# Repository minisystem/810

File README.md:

SYSTEM80 810
======================================

VCO/VCF/VCA in Eurorack format. Currently under development.

Hardware design by Minisystem: info@system80.net

LICENSE
=======
cc by-nc-sa
https://creativecommons.org/licenses/by-nc-sa/4.0/

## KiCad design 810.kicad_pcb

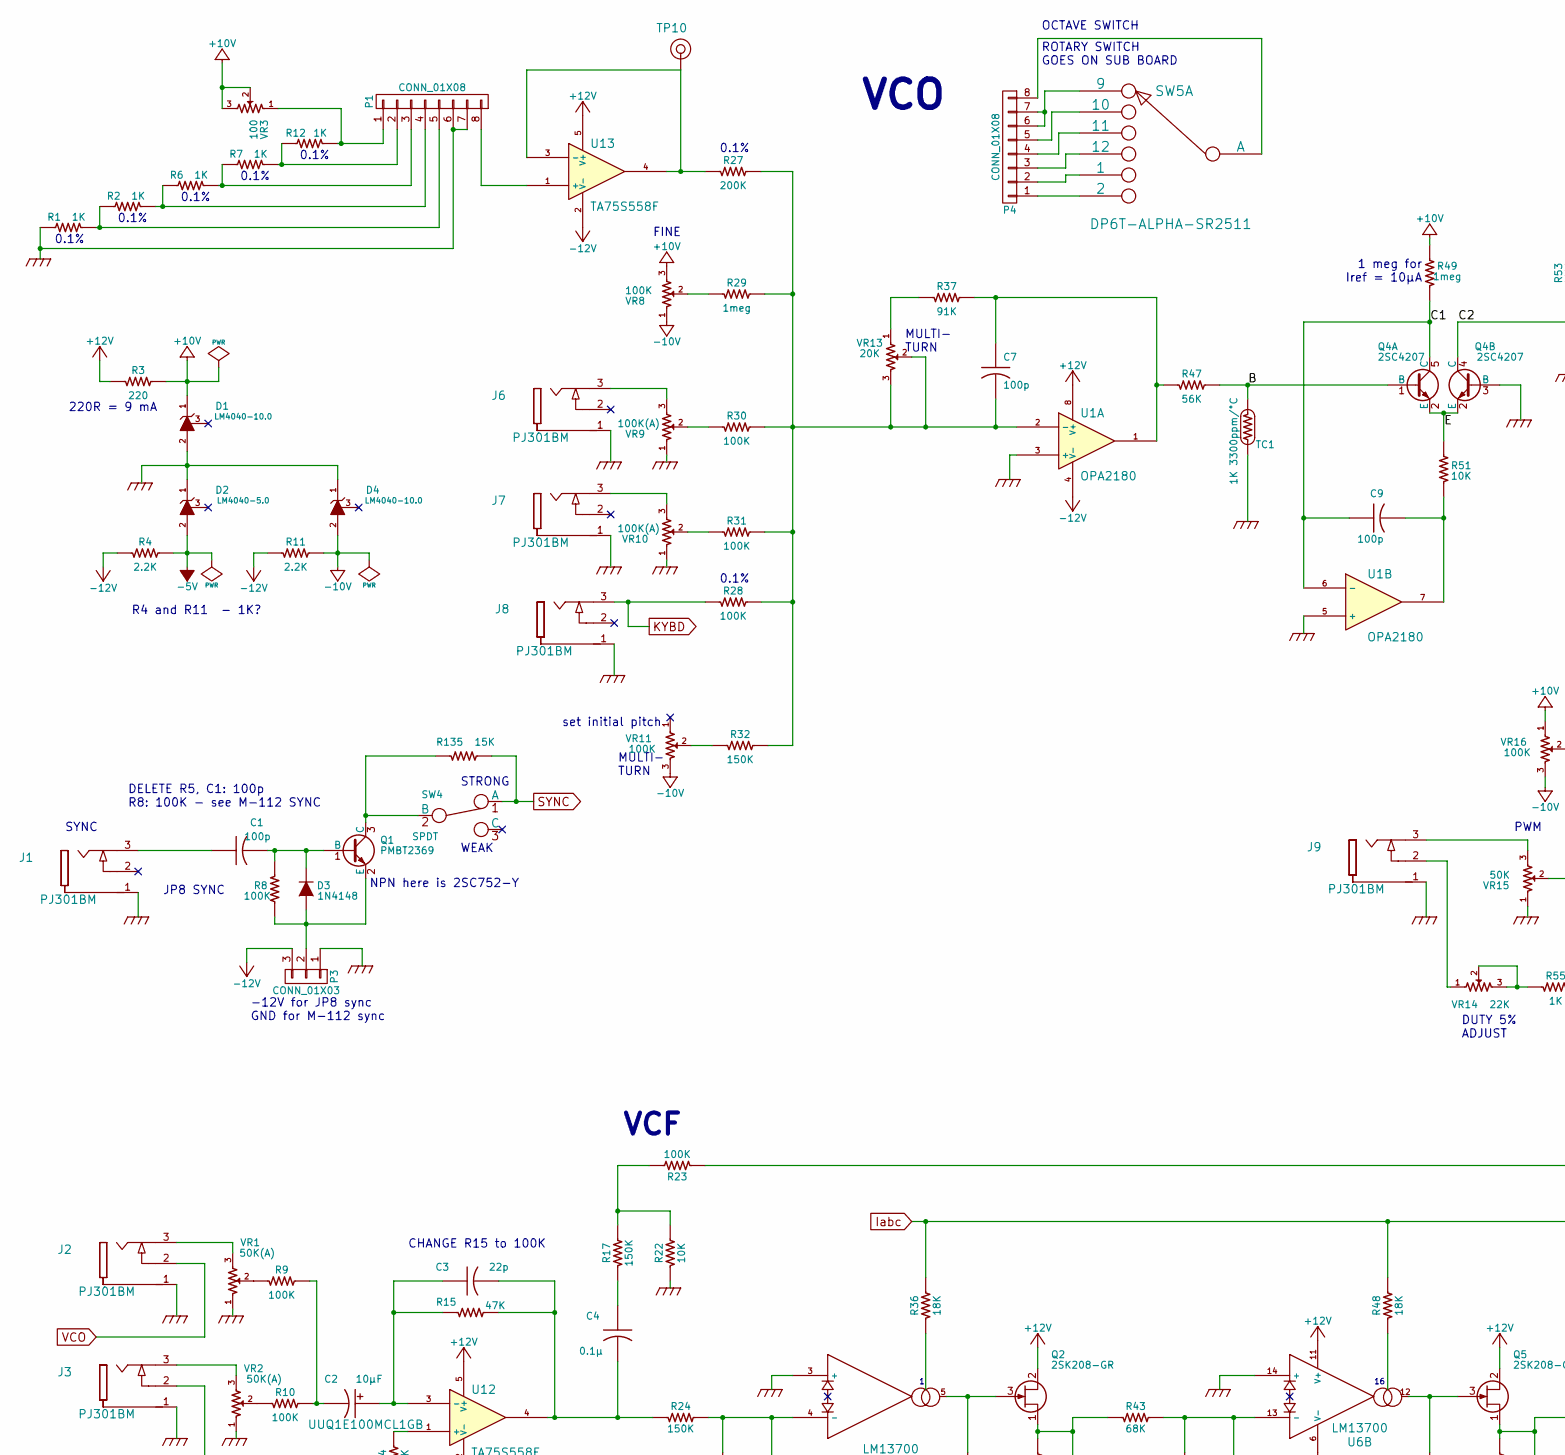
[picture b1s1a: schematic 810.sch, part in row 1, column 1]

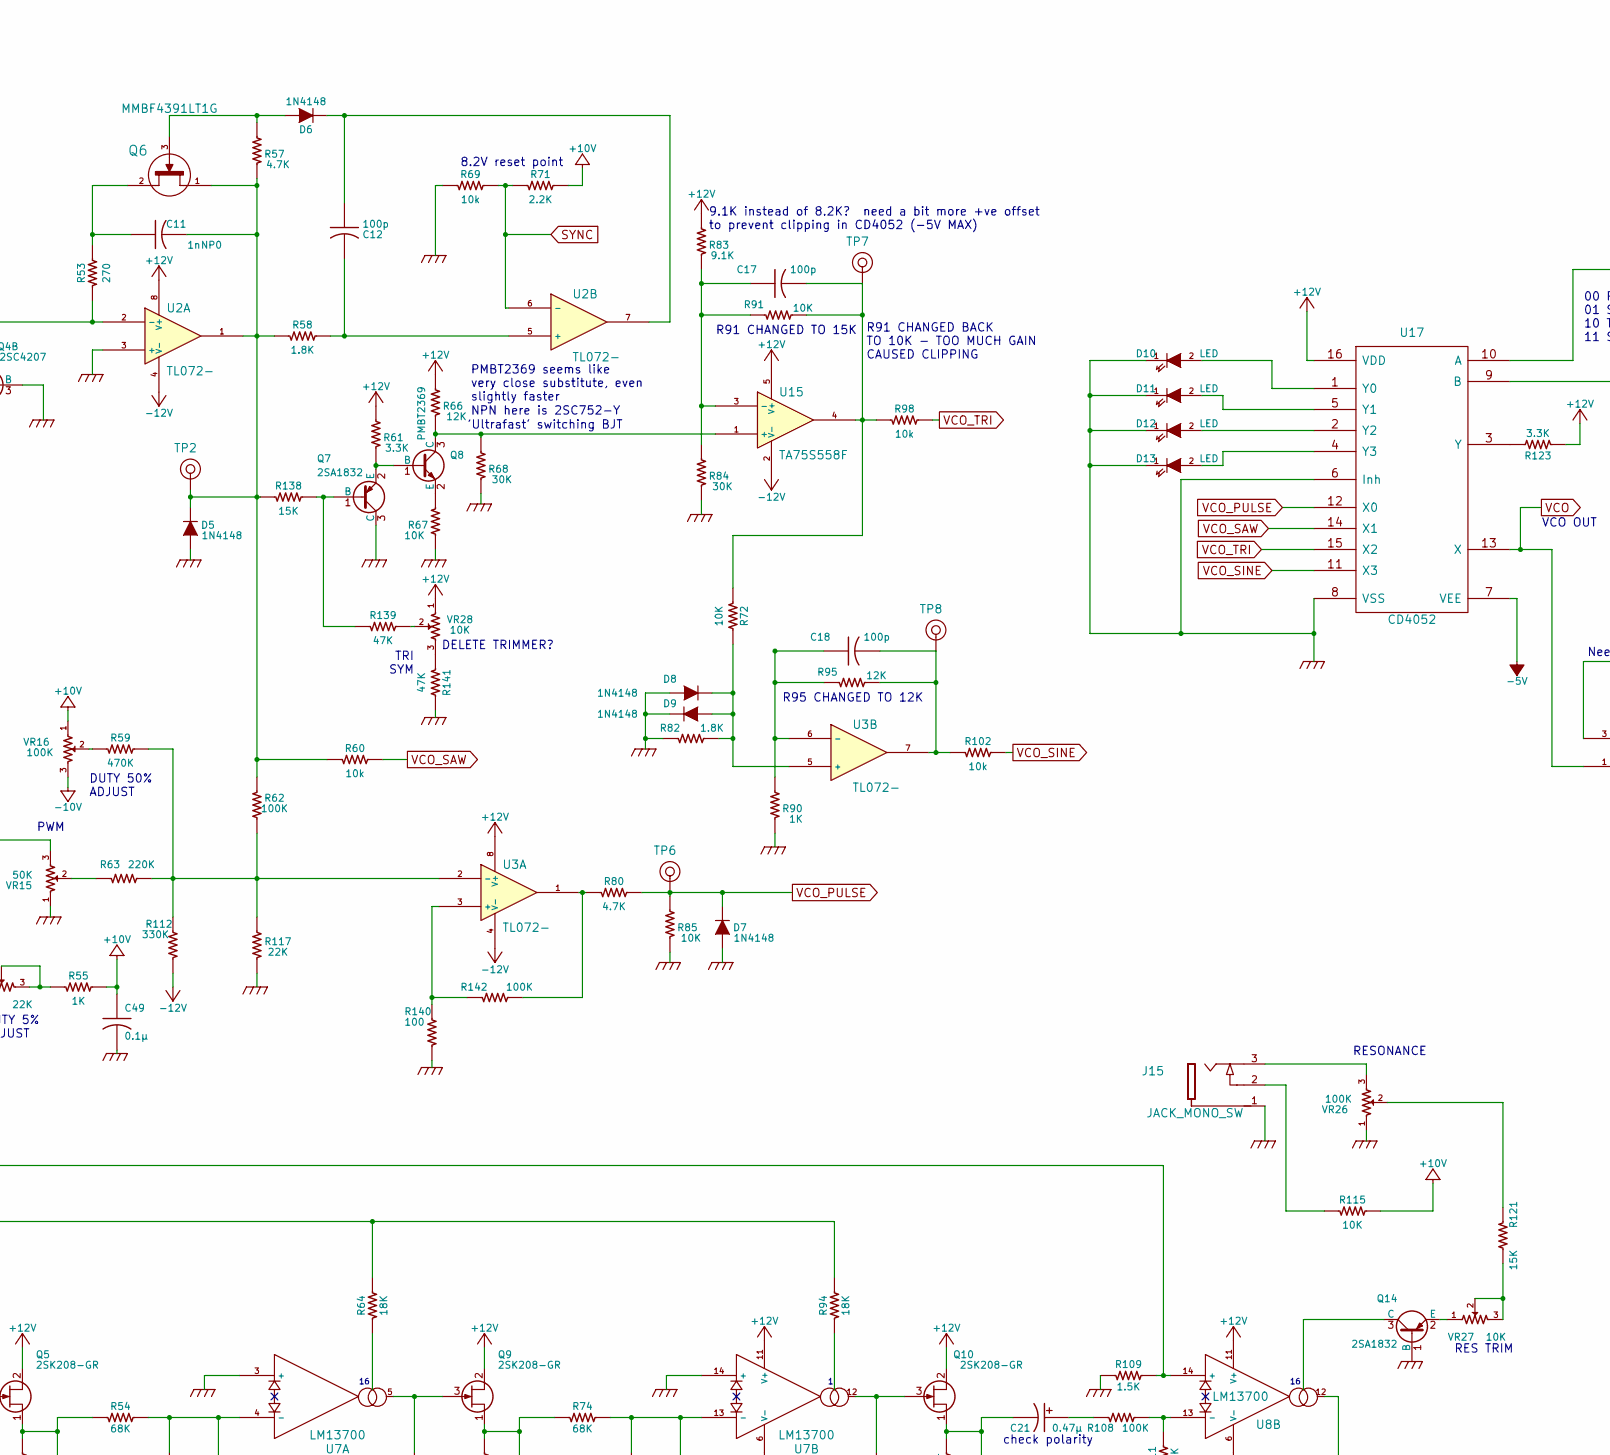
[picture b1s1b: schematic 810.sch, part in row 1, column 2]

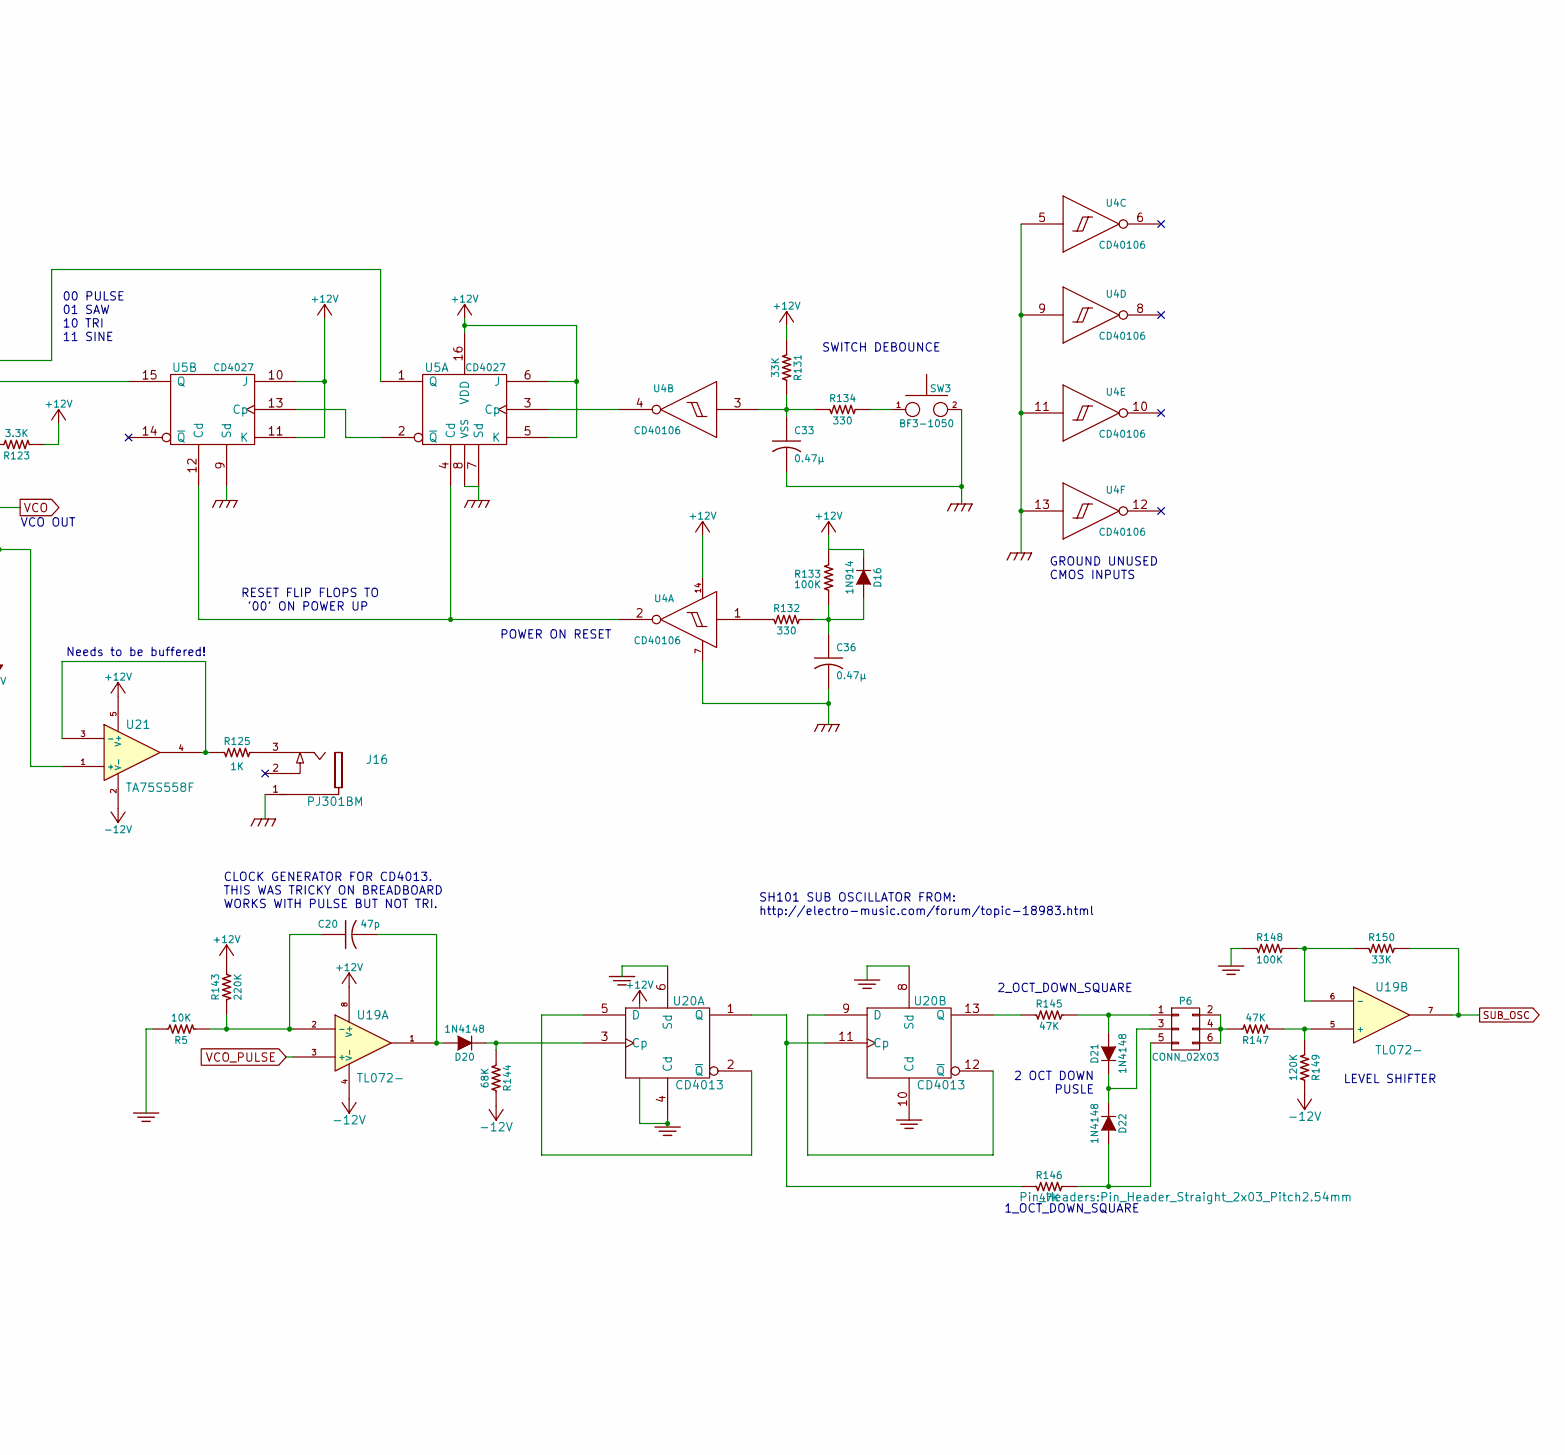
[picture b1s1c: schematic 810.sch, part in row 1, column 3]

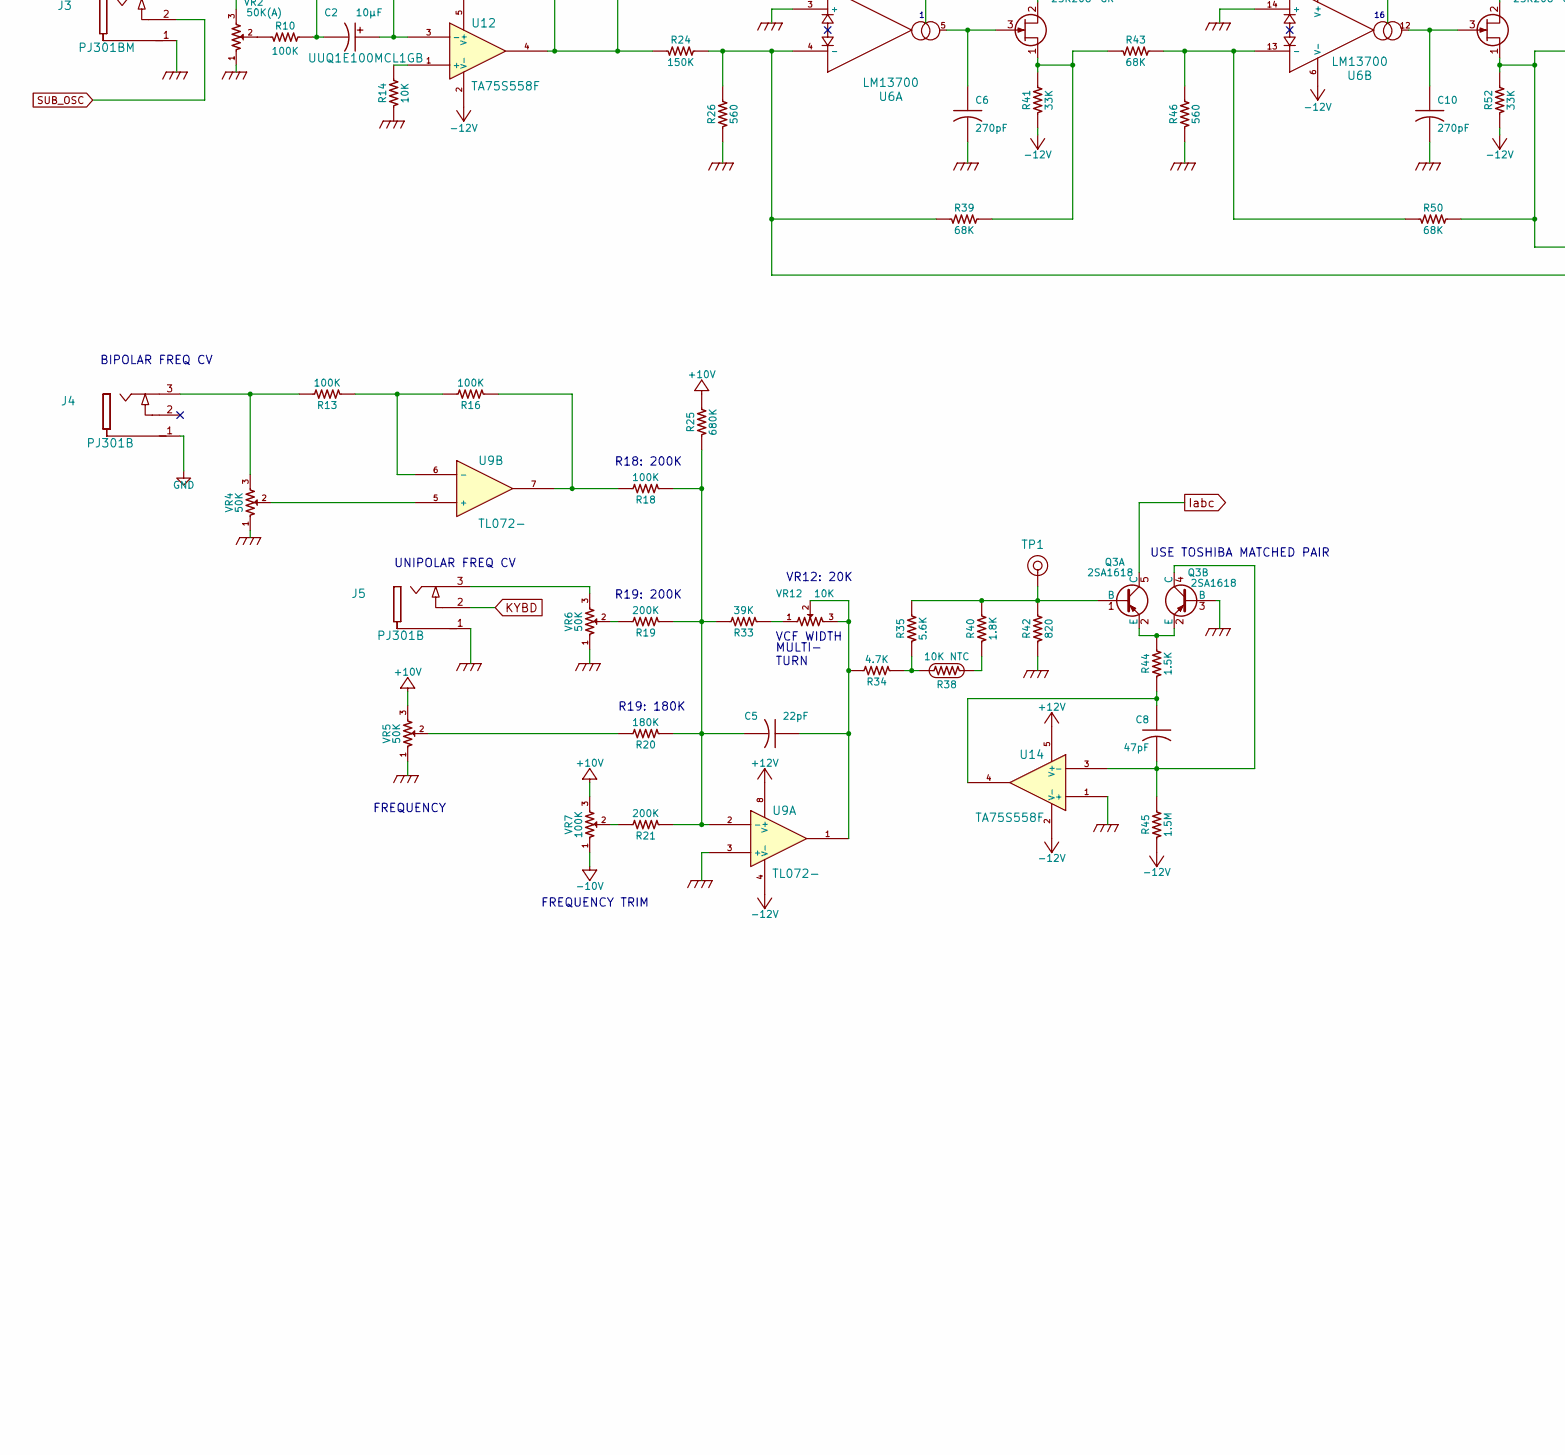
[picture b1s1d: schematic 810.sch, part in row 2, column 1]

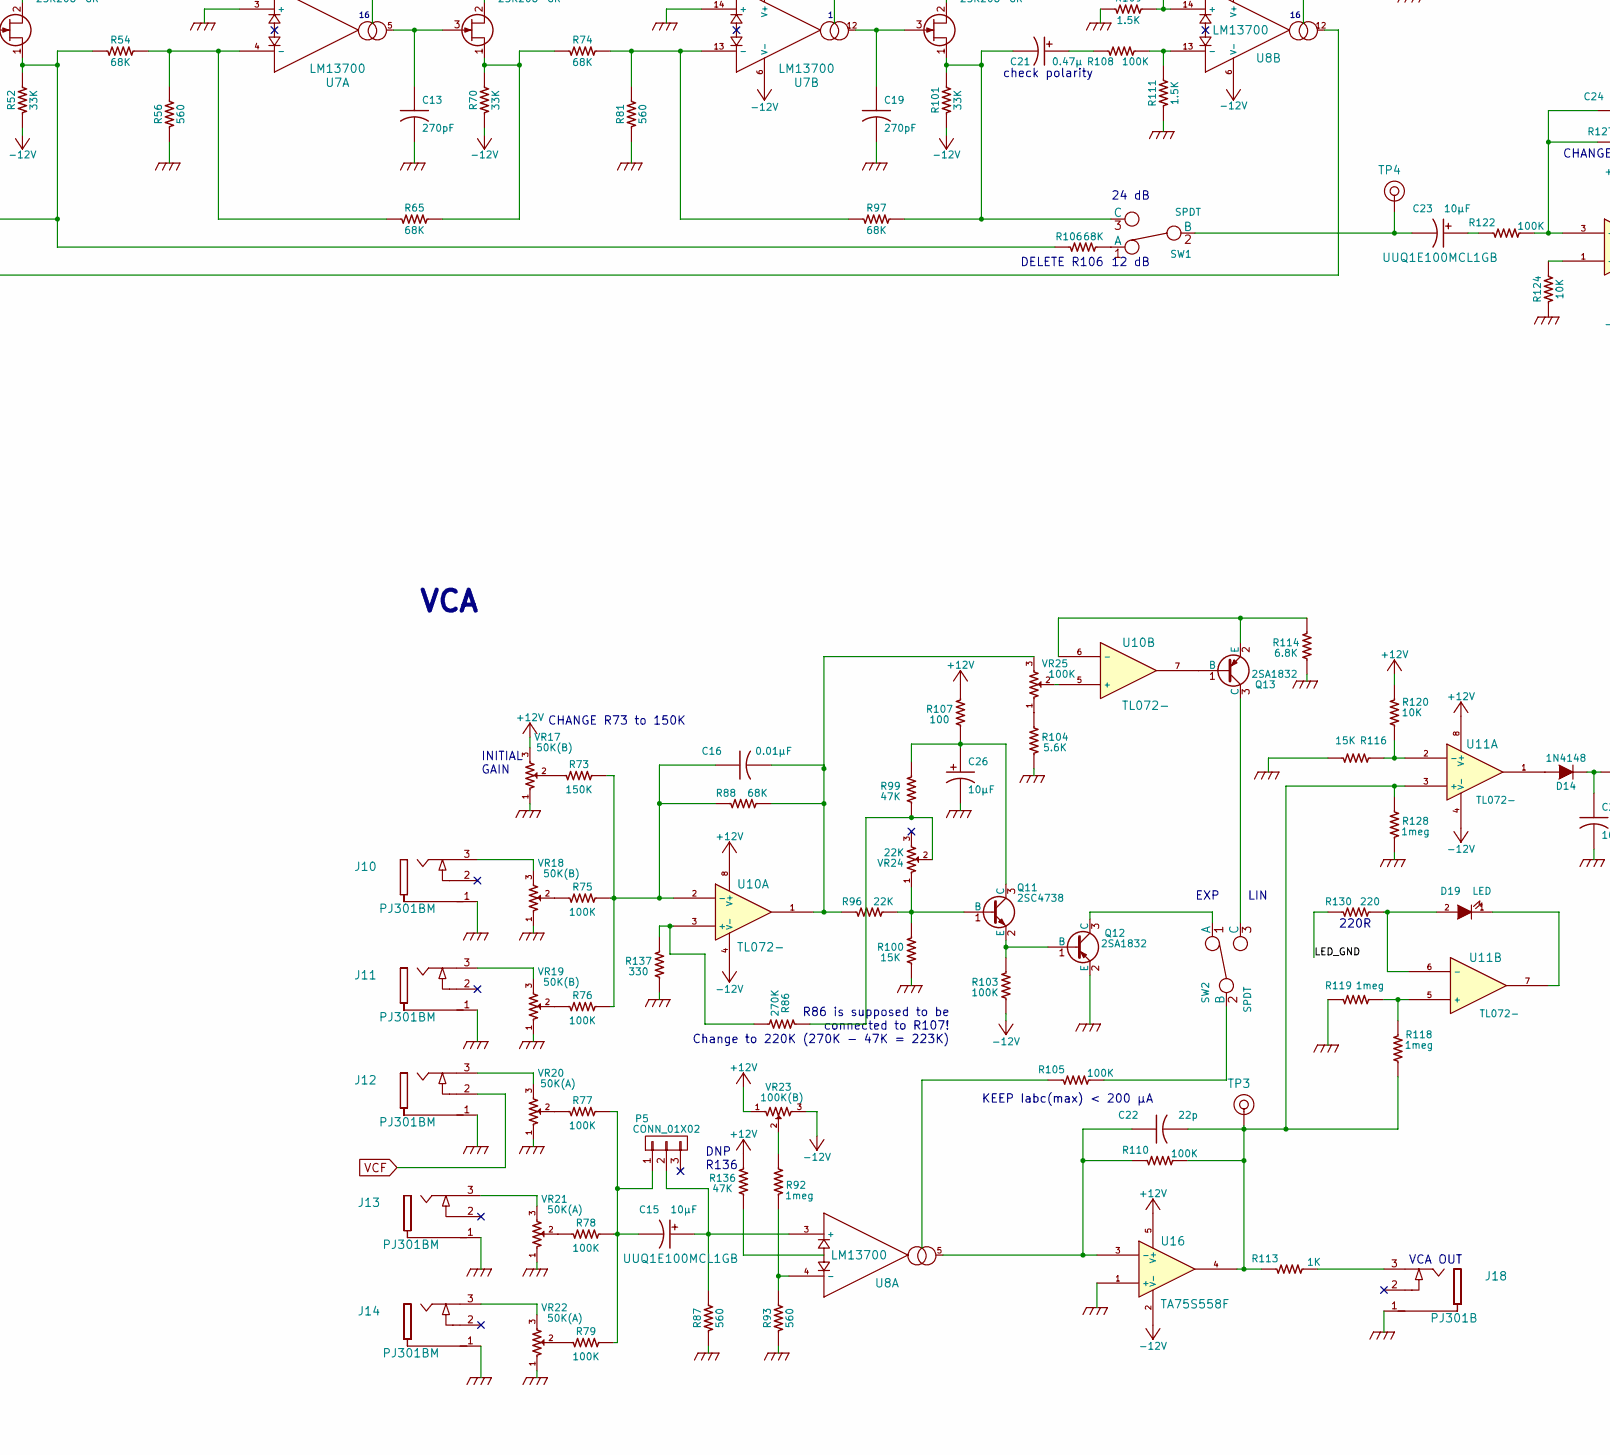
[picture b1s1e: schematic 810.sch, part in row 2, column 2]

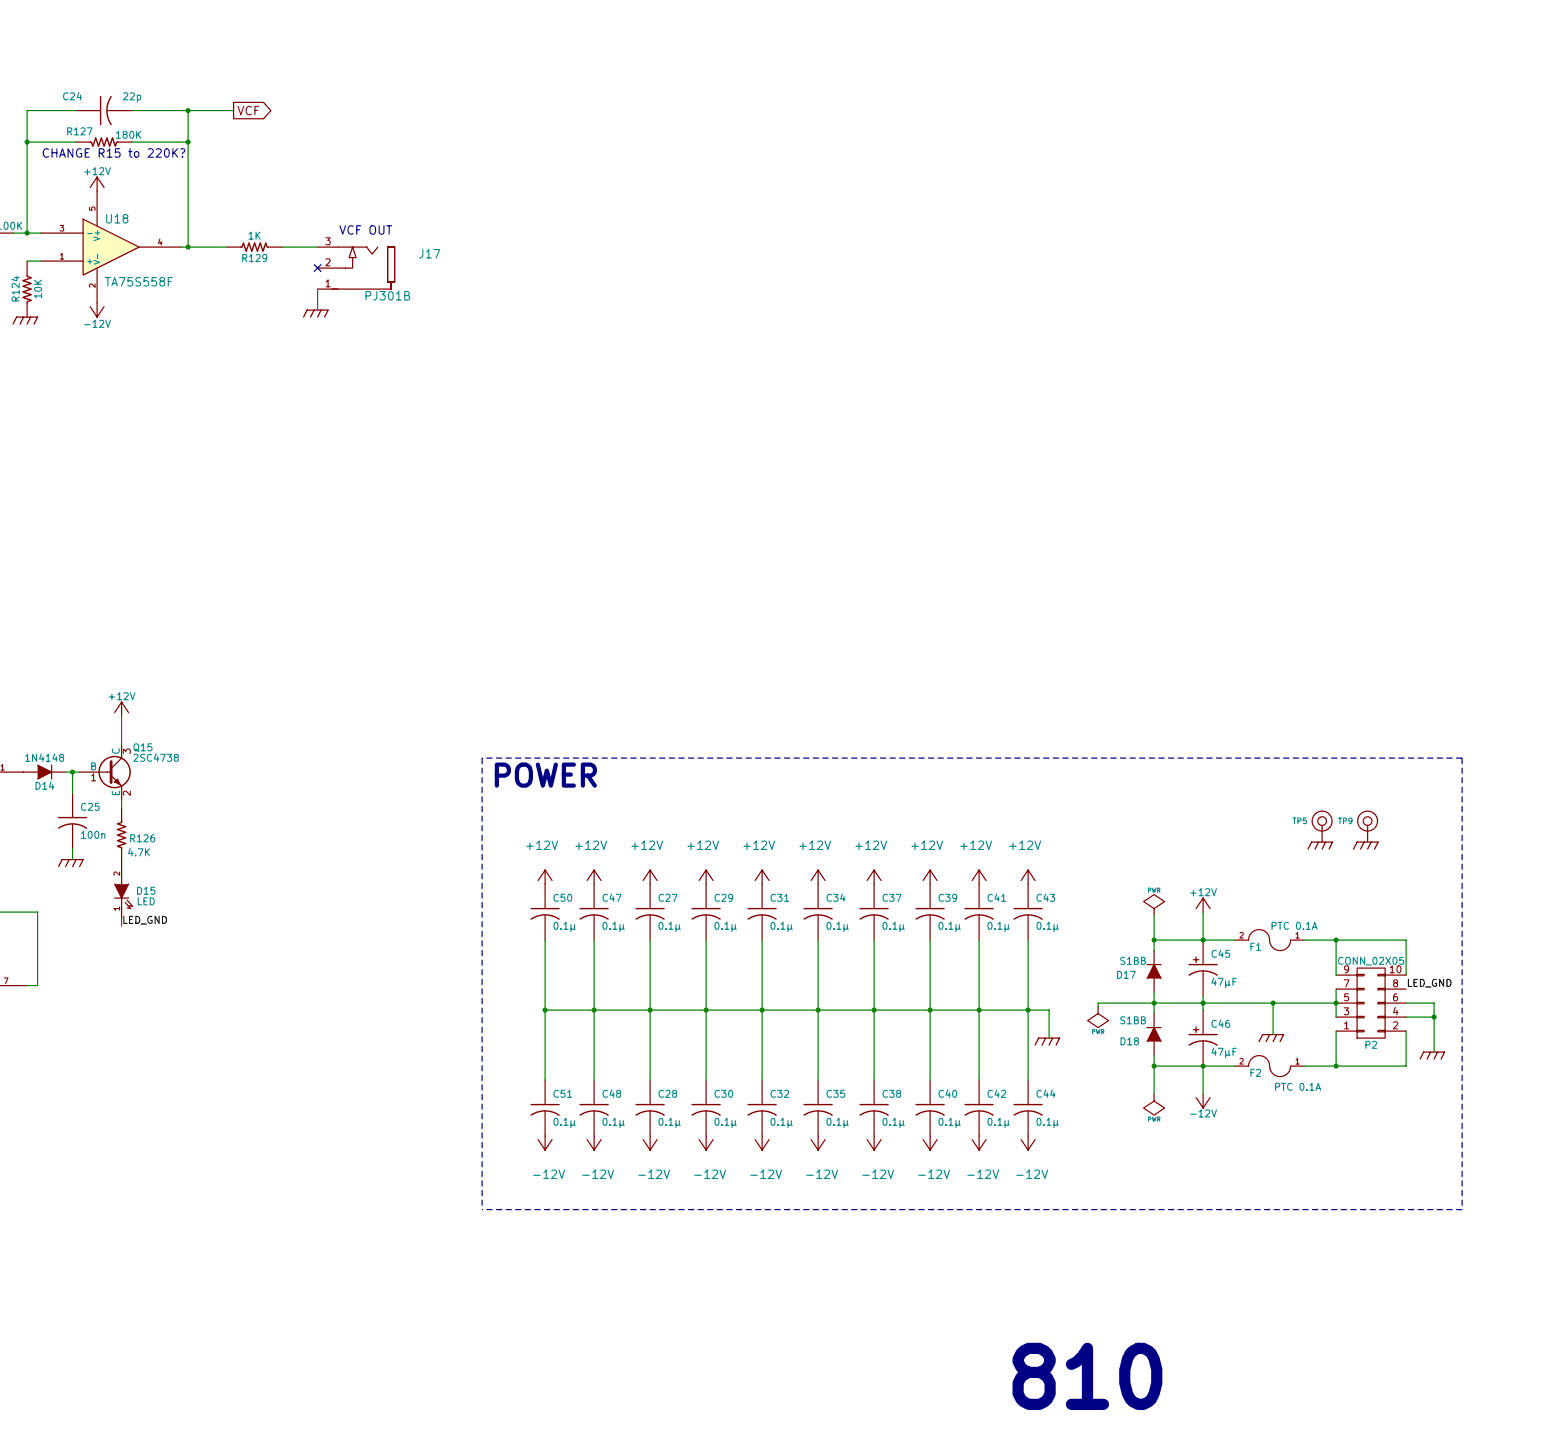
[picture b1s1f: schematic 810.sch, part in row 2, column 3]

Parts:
C1, C12, C17, C18: 100p; SM0603-C-JRL
C2, C15, C23: 10μF; jrl_c_elec_5x5.3; Part Number UUQ1E100MCL1GB
C3, C22, C24: 22p; SM0603-C-JRL
C4: 0.1μ; SM0603-C-JRL
C5: 22pF; SM0603-C-JRL
C6, C10, C13, C19: 270pF; SM0603-C-JRL
C7, C9: 100p; SM0603-C-JRL; Digikey 399-1122-1-ND
C8: 47pF; SM0603-C-JRL
C11: 1n; SM0603-C-JRL
C16: 0.01μF; SM0603-C-JRL
C20: 47p; SM0603-C-JRL
C21: 0.47μ; jrl_c_elec_4x5.3
C25: 100n; SM0603-C-JRL
C26: 10μF; jrl_c_elec_5x5.3
C27, C28, C29, C30, C31, C32, C34, C35, C37, C38, C39, C40, C41, C42, C43, C44, C47, C48, C49, C50, C51: 0.1µ; SM0603-C-JRL
C33, C36: 0.47μ; SM0603-C-JRL
C45, C46: 47μF; jrl_c_elec_5x5.3
D1, D4: LM4040-10.0; SOT23-132-JRL
D2: LM4040-5.0; SOT23-132-JRL
D3, D5, D6, D7, D8, D9, D14, D20, D21, D22: 1N4148; SOD323-C1A2
D10, D11, D12, D13, D15, D19: LED; 3MM-LED-C1A2
D16: 1N914; SOD323-C1A2
D17, D18: S1BB; SMB-1C2A
F1, F2: PTC 0.1A; C_0805
J1, J2, J3, J6, J7, J8, J9, J10, J11, J12, J13, J14, J16: PJ301BM; PJ-301B-JACK-SLOTS
J4, J5, J17, J18: PJ301B; PJ-301B-JACK-SLOTS
J15: JACK_MONO_SW; PJ-301B-JACK-SLOTS
P1, P4: CONN_01X08; Pin_Header_Straight_1x08_Pitch2.54mm
P2: CONN_02X05; Pin_Header_Straight_2x05_Pitch2.54mm
P3: CONN_01X03; Pin_Header_Straight_1x03_Pitch2.54mm
P5: CONN_01X02; Pin_Header_Straight_1x03_Pitch2.54mm
P6: CONN_02X03; Pin_Header_Straight_2x03_Pitch2.54mm
Q1: PMBT2369; SOT-23
Q2, Q9, Q10: 2SK208-GR; SOT-23
Q3: 2SA1618; SOT753_TSOP5_SC-74A
Q4: 2SC4207; SOT753_TSOP5_SC-74A
Q5: 2SK208-GR; SC-59
Q6: MMBF4391LT1G; SOT23-132-JRL
Q7, Q12, Q13, Q14: 2SA1832; SOT416-SC75
Q8: PMBT2369; SOT23-132-JRL
Q11, Q15: 2SC4738; SOT416-SC75
R1, R2, R6, R7, R12, R129: 1K; SM0603-R-JRL
R3: 220; SM0603-R-JRL; Digikey P10.0KCCT-ND
R4, R11, R71: 2.2K; SM0603-R-JRL; Digikey P10.0KCCT-ND
R5, R14, R22, R124: 10K; SM0603-R-JRL
R8, R62, R105, R110, R122, R142: 100K; SM0603-R-JRL; Digikey P10.0KCCT-ND
R9, R10, R28, R30, R31, R75, R76, R77, R78, R79: 100K; SM0603-R-JRL; Digikey P91.0KCCT-ND
R13, R16, R18, R23, R103, R108, R133, R148: 100K; SM0603-R-JRL
R15, R139, R141: 47K; SM0603-R-JRL; Digikey P10.0KCCT-ND
R17, R24: 150K; SM0603-R-JRL
R19, R21: 200K; SM0603-R-JRL
R20: 180K; SM0603-R-JRL
R25: 680K; SM0603-R-JRL
R26, R46, R56, R81, R87, R93: 560; SM0603-R-JRL
R27: 200K; SM0603-R-JRL; Digikey P91.0KCCT-ND
R29: 1meg; SM0603-R-JRL; Digikey P91.0KCCT-ND
R32, R73: 150K; SM0603-R-JRL; Digikey P91.0KCCT-ND
R33: 39K; SM0603-R-JRL
R34: 4.7K; SM0603-R-JRL
R35, R104: 5.6K; SM0603-R-JRL
R36, R48, R64, R94: 18K; SM0603-R-JRL
R37: 91K; SM0603-R-JRL; Digikey P91.0KCCT-ND
R38: 10K NTC; SM0805-HAND
R39, R43, R50, R54, R65, R74, R97, R106, R144: 68K; SM0603-R-JRL
R40: 1.8K; SM0603-R-JRL
R41, R52, R70, R101, R131, R150: 33K; SM0603-R-JRL
R42: 820; SM0603-R-JRL
R44, R109, R111: 1.5K; SM0603-R-JRL
R45: 1.5M; SM0603-R-JRL
R47: 56K; SM0603-R-JRL; Digikey P56.0KCCT-ND
R49: 1meg; SM0603-R-JRL; Digikey P1.50MCCT-ND
R51, R67, R72, R85, R91, R115: 10K; SM0603-R-JRL; Digikey P10.0KCCT-ND
R53: 270; SM0603-R-JRL; Digikey P10.0KCCT-ND
R55, R90, R113, R125: 1K; SM0603-R-JRL; Digikey P10.0KCCT-ND
R57, R80, R126: 4.7K; SM0603-R-JRL; Digikey P10.0KCCT-ND
R58, R82: 1.8K; SM0603-R-JRL; Digikey P10.0KCCT-ND
R59: 470K; SM0603-R-JRL; Digikey P10.0KCCT-ND
R60, R69, R98, R102: 10k; SM0603-R-JRL; Digikey P10.0KCCT-ND
R61: 3.3K; SM0603-R-JRL; Digikey P10.0KCCT-ND
R63: 220K; SM0603-R-JRL; Digikey P10.0KCCT-ND
R66, R95: 12K; SM0603-R-JRL; Digikey P10.0KCCT-ND
R68, R84: 30K; SM0603-R-JRL; Digikey P10.0KCCT-ND
R83: 9.1K; SM0603-R-JRL; Digikey P10.0KCCT-ND
R86: 270K; SM0603-R-JRL
R88: 68K; SM0603-R-JRL; Digikey P91.0KCCT-ND
R92, R128: 1meg; SM0603-R-JRL
R96: 22K; SM0603-R-JRL; Digikey P91.0KCCT-ND
R99, R136, R145, R146, R147: 47K; SM0603-R-JRL
R100, R116: 15K; SM0603-R-JRL
R107: 100; SM0603-R-JRL
R112: 330K; SM0603-R-JRL; Digikey P10.0KCCT-ND
R114: 6.8K; SM0603-R-JRL
R117: 22K; SM0603-R-JRL
R118, R119: 1meg; SM0603-R-JRL; Digikey P10.0KCCT-ND
R120: 10K; SM0603-R-JRL; Digikey P91.0KCCT-ND
R121, R135, R138: 15K; SM0603-R-JRL; Digikey P10.0KCCT-ND
R123: 3.3K; SM0603-R-JRL
R127: 180K; SM0603-R-JRL; Digikey P10.0KCCT-ND
R130: 220; SM0603-R-JRL; Digikey P91.0KCCT-ND
R132, R134, R137: 330; SM0603-R-JRL
R140: 100; SM0603-R-JRL; Digikey P10.0KCCT-ND
R143: 220K; SM0603-R-JRL
R149: 120K; SM0603-R-JRL
SW1, SW2, SW4: SPDT; SS-12F108-1P2T-SLIDE
SW3: BF3-1050; B3F-1050-OMRON
SW5: DP6T-ALPHA-SR2511; SR2511-ALPHA
TC1: 1K 3300ppm/°C; SM0603-R-YAGEO
TP1, TP2, TP3, TP4, TP6, TP7, TP8, TP10: TEST_POINT; TEST_POINT_5000_SERIES
TP5, TP9: CONN_1; TEST_POINT_LOOP_4592
U1: OPA2180; TSSOP8-JRL
U2, U3, U9, U10, U19: TL072-; TSSOP8-JRL
U4: CD40106; TSSOP-14_4.4x5mm_Pitch0.65mm
U5: CD4027; TSSOP-16_4.4x5mm_Pitch0.65mm
U6, U7, U8: LM13700; SO16-JRL
U11: TL072-; TSSOP-8_4.4x3mm_Pitch0.65mm
U12, U13, U14, U15, U16, U18, U21: TA75S558F; SOT753_TSOP5_SC-74A
U17: CD4052; TSSOP-16_4.4x5mm_Pitch0.65mm
U20: CD4013; TSSOP-14_4.4x5mm_Pitch0.65mm
VR1, VR2, VR20, VR21, VR22: 50K(A); RD901F-ALPHA-POT-T18
VR3: 100; TC33X-2
VR4, VR5, VR6, VR15: 50K; RD901F-ALPHA-POT-T18
VR7, VR11, VR16, VR25: 100K; TC33X-2
VR8, VR26: 100K; RD901F-ALPHA-POT-T18
VR9, VR10: 100K(A); RD901F-ALPHA-POT-T18
VR12: 10K; Bourns-3296W
VR13: 20K; Bourns-3296W
VR14, VR24: 22K; TC33X-2
VR17, VR18, VR19: 50K(B); RD901F-ALPHA-POT-T18
VR23: 100K(B); TC33X-2
VR27, VR28: 10K; TC33X-2

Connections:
+10V: C49.1, D1.1 (K), R3.2, R25.2, R49.2, R55.2, R71.2, R115.2, VR3.2, VR3.3, VR5.3, VR7.3, VR8.3, VR16.1
+12V: C27.1, C29.1, C31.1, C34.1, C37.1, C39.1, C41.1, C43.1, C45.1 (+), C47.1, C50.1, D16.1 (K), D17.1 (K), F1.2, Q2.2 (S), Q5.2 (S), Q9.2 (S), Q10.2 (S), Q15.3 (C), R3.1, R61.2, R66.2, R83.2, R107.2, R120.1, R123.1, R131.2, R133.2, R136.2, R143.2, U1.8 (V+), U2.8 (V+), U3.8 (V+), U4.14 (VDD), U5.5 (K), U5.6 (J), U5.10 (J), U5.11 (K), U5.16 (VDD), U6.11 (V+), U7.11 (V+), U8.11 (V+), U9.8 (V+), U10.8 (V+), U11.8 (V+), U12.5 (V+), U13.5 (V+), U14.5 (V+), U15.5 (V+), U16.5 (V+), U17.16 (VDD), U18.5 (V+), U19.8 (V+), U20.14 (VDD), U21.5 (V+), VR17.3, VR23.1, VR28.1
-5V: D2.2 (A), R4.2, U17.7 (VEE)
-10V: D4.2 (A), R11.2, VR7.1, VR8.1, VR11.3, VR16.3
-12V: C28.2, C30.2, C32.2, C35.2, C38.2, C40.2, C42.2, C44.2, C46.2 (-), C48.2, C51.2, D18.2 (A), F2.2, P3.3, R4.1, R11.1, R41.1, R45.2, R52.1, R70.1, R101.1, R103.1, R112.2, R144.2, R149.2, U1.4 (V-), U2.4 (V-), U3.4 (V-), U6.6 (V-), U7.6 (V-), U8.6 (V-), U9.4 (V-), U10.4 (V-), U11.4 (V-), U12.2 (V-), U13.2 (V-), U14.2 (V-), U15.2 (V-), U16.2 (V-), U18.2 (V-), U19.4 (V-), U21.2 (V-), VR23.3
/B: Q4.1 (B), R47.2, TC1.1
/C1: C9.1, Q4.5 (C), R49.1, U1.6 (-)
/C2: Q4.4 (C), R53.1, U2.2 (-)
/E: Q4.2 (E), R51.2
/LED_GND: D15.1 (K), P2.8, R130.1
Iabc: Q3.5 (C), R36.2, R48.2, R64.2, R94.2
KYBD: J5.2, J8.3, R28.1
unnamed: C1.1, J1.3
unnamed: C1.2, D3.1 (K), Q1.1 (B), R8.2
unnamed: C2.1 (+), C3.1, R15.1, U12.3 (-)
unnamed: C2.2 (-), R9.2, R10.2
unnamed: C3.2, C4.2, R15.2, R24.1, U12.4
unnamed: C4.1, R17.1
unnamed: C5.1, R34.2, U9.1, VR12.2, VR12.3
unnamed: C5.2, R18.1, R19.1, R20.1, R21.1, R25.1, R33.2, U9.2 (-)
unnamed: C6.1, Q2.3 (G), U6.5
unnamed: C7.1, R37.2, R47.1, U1.1
unnamed: C7.2, R27.2, R28.2, R29.2, R30.2, R31.2, R32.2, U1.2 (-), VR13.2, VR13.3
unnamed: C8.1, R44.2, U14.4
unnamed: C8.2, Q3.4 (C), R45.1, U14.3 (-)
unnamed: C9.2, R51.1, U1.7
unnamed: C10.1, Q5.3 (G), U6.12
unnamed: C11.1, Q6.2 (S), R53.2
unnamed: C11.2, D5.1 (K), Q6.1 (D), R57.1, R58.1, R60.1, R62.1, R138.1, TP2.1, U2.1
unnamed: C12.1, D6.1 (K), U2.7
unnamed: C12.2, R58.2, U2.5 (+)
unnamed: C13.1, Q9.3 (G), U7.5
unnamed: C15.1 (+), P5.2, R87.2, U8.3 (+)
unnamed: C15.2 (-), P5.1, R77.2, R78.2, R79.2
unnamed: C16.1, R73.2, R75.2, R76.2, R88.1, U10.2 (-)
unnamed: C16.2, R88.2, R96.1, U10.1, VR25.3
unnamed: C17.1, R83.1, R84.2, R91.1, U15.3 (-)
unnamed: C17.2, R72.1, R91.2, R98.1, TP7.1, U15.4
unnamed: C18.1, R90.2, R95.1, U3.6 (-)
unnamed: C18.2, R95.2, R102.1, TP8.1, U3.7
unnamed: C19.1, Q10.3 (G), U7.12
unnamed: C20.1, R5.1, R143.1, U19.2 (-)
unnamed: C20.2, D20.2 (A), U19.1
unnamed: C21.1 (+), R108.2
unnamed: C21.2 (-), Q10.1 (D), R97.1, R101.2, SW1.3 (C)
unnamed: C22.1, R110.1, U8.5, U16.3 (-)
unnamed: C22.2, R110.2, R113.1, R118.2, R128.2, TP3.1, U11.3 (+), U16.4
unnamed: C23.1 (+), R122.1
unnamed: C23.2 (-), SW1.2 (B), TP4.1
unnamed: C24.1, R122.2, R127.1, U18.3 (-)
unnamed: C25.1, D14.1 (K), Q15.1 (B)
unnamed: C26.1 (+), Q11.3 (C), R99.2, R107.1
unnamed: C33.1, R131.1, R134.1, U4.3 (In)
unnamed: C36.1, D16.2 (A), R132.2, R133.1
unnamed: D3.2 (A), P3.2, Q1.2 (E), R8.1
unnamed: D6.2 (A), Q6.3 (G), R57.2
unnamed: D8.1 (K), D9.2 (A), R72.2, R82.2, U3.5 (+)
unnamed: D10.2 (A), U17.1 (Y0)
unnamed: D11.2 (A), U17.5 (Y1)
unnamed: D12.2 (A), U17.2 (Y2)
unnamed: D13.2 (A), U17.4 (Y3)
unnamed: D14.2 (A), U11.1
unnamed: D15.2 (A), R126.2
unnamed: D19.1 (K), U11.7
unnamed: D19.2 (A), R130.2, U11.6 (-)
unnamed: D20.1 (K), R144.1, U20.3 (Cp)
unnamed: D21.1 (K), D22.1 (K), P6.3
unnamed: D21.2 (A), P6.1, R145.2
unnamed: D22.2 (A), P6.5, R146.2
unnamed: F1.1, P2.9, P2.10
unnamed: F2.1, P2.1, P2.2
unnamed: J2.3, VR1.3
unnamed: J3.3, VR2.3
unnamed: J4.3, R13.2, VR4.3
unnamed: J5.3, VR6.3
unnamed: J6.3, VR9.3
unnamed: J7.3, VR10.3
unnamed: J9.2, VR14.1
unnamed: J9.3, VR15.3
unnamed: J10.3, VR18.3
unnamed: J11.3, VR19.3
unnamed: J12.3, VR20.3
unnamed: J13.3, VR21.3
unnamed: J14.3, VR22.3
unnamed: J15.2, R115.1
unnamed: J15.3, VR26.3
unnamed: J16.3, R125.2
unnamed: J17.3, R129.1
unnamed: J18.3, R113.2
unnamed: P1.1, R12.1, VR3.1
unnamed: P1.2, R7.1, R12.2
unnamed: P1.3, R6.1, R7.2
unnamed: P1.4, R2.1, R6.2
unnamed: P1.5, R1.1, R2.2
unnamed: P1.8, U13.1 (+)
unnamed: P4.1, SW5.2
unnamed: P4.2, SW5.1
unnamed: P4.3, SW5.12
unnamed: P4.4, SW5.11
unnamed: P4.5, SW5.10
unnamed: P4.6, P4.7, SW5.9
unnamed: P4.8, SW5.A
unnamed: P6.2, P6.4, P6.6, R147.2
unnamed: Q1.3 (C), R135.1, SW4.2 (B)
unnamed: Q2.1 (D), R39.1, R41.2, R43.2
unnamed: Q3.1 (B), R35.2, R40.2, R42.2, TP1.1
unnamed: Q3.2 (E), R44.1
unnamed: Q5.1 (D), R50.1, R52.2, R54.2, R106.2
unnamed: Q7.1 (B), R138.2, R139.2
unnamed: Q7.2 (E), Q8.1 (B), R61.1
unnamed: Q8.2 (E), R67.2
unnamed: Q8.3 (C), R66.1, R68.2, U15.1 (+)
unnamed: Q9.1 (D), R65.1, R70.2, R74.2
unnamed: Q11.1 (B), R96.2, R100.2, VR24.1
unnamed: Q11.2 (E), Q12.1 (B), R103.2
unnamed: Q12.3 (C), SW2.1 (A)
unnamed: Q13.1 (B), U10.7
unnamed: Q13.2 (E), R114.2, U10.6 (-)
unnamed: Q13.3 (C), SW2.3 (C)
unnamed: Q14.2 (E), VR27.1
unnamed: Q14.3 (C), U8.16
unnamed: Q15.2 (E), R126.1
unnamed: R9.1, VR1.2
unnamed: R10.1, VR2.2
unnamed: R13.1, R16.2, U9.6 (-)
unnamed: R14.2, U12.1 (+)
unnamed: R16.1, R18.2, U9.7
unnamed: R17.2, R22.2, R23.2
unnamed: R19.2, VR6.2
unnamed: R20.2, VR5.2
unnamed: R21.2, VR7.2
unnamed: R24.2, R26.2, R39.2, U6.4 (-), U8.12
unnamed: R27.1, TP10.1, U13.3 (-), U13.4
unnamed: R29.1, VR8.2
unnamed: R30.1, VR9.2
unnamed: R31.1, VR10.2
unnamed: R32.1, VR11.2
unnamed: R33.1, VR12.1
unnamed: R34.1, R35.1, R38.2
unnamed: R36.1, U6.1
unnamed: R37.1, VR13.1
unnamed: R38.1, R40.1
unnamed: R43.1, R46.2, R50.2, U6.13 (-)
unnamed: R48.1, U6.16
unnamed: R54.1, R56.2, R65.2, U7.4 (-)
unnamed: R55.1, VR14.2, VR14.3
unnamed: R59.1, VR16.2
unnamed: R63.1, VR15.2
unnamed: R64.1, U7.1
unnamed: R73.1, VR17.2
unnamed: R74.1, R81.2, R97.2, U7.13 (-)
unnamed: R75.1, VR18.2
unnamed: R76.1, VR19.2
unnamed: R77.1, VR20.2
unnamed: R78.1, VR21.2
unnamed: R79.1, VR22.2
unnamed: R86.2, R99.1, VR24.2
unnamed: R92.1, R93.2, U8.4 (-)
unnamed: R92.2, VR23.2
unnamed: R94.1, U7.16
unnamed: R104.2, VR25.1
unnamed: R105.1, U8.1
unnamed: R105.2, SW2.2 (B)
unnamed: R106.1, SW1.1 (A)
unnamed: R108.1, R111.2, U8.13 (-)
unnamed: R23.1, R109.1, U8.14 (+)
unnamed: R59.2, R62.2, R63.2, R112.1, R117.2, U3.2 (-)
unnamed: R116.2, R120.2, U11.2 (-)
unnamed: R118.1, R119.2, U11.5 (+)
unnamed: R121.1, VR26.2
unnamed: R121.2, VR27.2, VR27.3
unnamed: R123.2, U17.3 (Y)
unnamed: R124.2, U18.1 (+)
unnamed: R125.1, U21.3 (-), U21.4
unnamed: R132.1, U4.1 (In)
unnamed: R134.2, SW3.1
unnamed: R136.1, U8.2
unnamed: R86.1, R137.2, U10.3 (+)
unnamed: R139.1, VR28.2
unnamed: R140.1, R142.1, U3.3 (+)
unnamed: R141.2, VR28.3
unnamed: R80.1, R142.2, U3.1
unnamed: R145.1, U20.13 (Q)
unnamed: R146.1, U20.1 (Q), U20.11 (Cp)
unnamed: R147.1, R149.1, U19.5 (+)
unnamed: R148.2, R150.1, U19.6 (-)
unnamed: U4.2 (Out), U5.4 (Cd), U5.12 (Cd)
unnamed: U4.4 (Out), U5.3 (Cp)
unnamed: U5.2 (~Q), U5.13 (Cp)
unnamed: U9.5 (+), VR4.2
unnamed: U10.5 (+), VR25.2
unnamed: U5.15 (Q), U17.9 (B)
unnamed: U5.1 (Q), U17.10 (A)
unnamed: U20.2 (~Q), U20.5 (D)
unnamed: U20.9 (D), U20.12 (~Q)
SUB_OSC: J3.2, R150.2, U19.7
SYNC: R69.2, R71.1, R135.2, SW4.1 (A), U2.6 (-); also elsewhere on the board
VCF: C24.2, J12.2, R127.2, R129.2, U18.4
VCO: J2.2, U17.13 (X), U21.1 (+)
VCO_PULSE: D7.1 (K), R80.2, R85.2, TP6.1, U17.12 (X0), U19.3 (+)
VCO_SAW: R60.2, U17.14 (X1)
VCO_SINE: R102.2, U17.11 (X3)
VCO_TRI: R98.2, U17.15 (X2)

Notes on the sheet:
VCO
NPN here is 2SC752-Y
8.2V reset point
'Ultrafast' switching BJT
PMBT2369 seems like very close substitute, even slightly faster
MULTI- TURN
set initial pitch
FINE
DUTY 50% ADJUST
DUTY 5% ADJUST
PWM
check polarity
VCF
FREQUENCY TRIM
FREQUENCY
BIPOLAR FREQ CV
UNIPOLAR FREQ CV
RESONANCE
RES TRIM
USE TOSHIBA MATCHED PAIR
00 PULSE 01 SAW 10 TRI 11 SINE
POWER ON RESET
SWITCH DEBOUNCE
GROUND UNUSED CMOS INPUTS
RESET FLIP FLOPS TO '00' ON POWER UP
VCF WIDTH
INITIAL GAIN
POWER
VCA
SYNC
ROTARY SWITCH GOES ON SUB BOARD
JP8 SYNC
810
VCA OUT
VCF OUT
VCO OUT
WEAK
STRONG
-12V for JP8 sync GND for M-112 sync
OCTAVE SWITCH

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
